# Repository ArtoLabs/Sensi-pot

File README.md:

#### Sensi-pot is open source hardware and software 
designed to help automate routine indoor garden processes such as lighting cycles, environment control, watering, and nutrient regulation. A prolific boom in the marijuana industry is taking place in Colorado, Oregon, and Washington states in the U.S. (and soon many other states) causing an increased demand for indoor gardening products. Especially in Colorado, where the winter is long and cold, most marijuana is grown indoors; necessitating equipment to help control and mimic the plant's native environment. This is especially needed for growing marijuana, which is very sensitive to heat and humidity (or lack thereof). However, most indoor gardening automation equipment is designed for big production facilities and is usually too expensive for the average grower. Sensi-pot provides electronics kits that can be easily assembled by anyone with a soldering iron, allowing the average user access to the same type of technology available to bigger growers at a fraction of the price.

# Sensi-Pot Indoor Environment Controller

This is the first Sensi-Pot open source automation device made for regulating the temperature and humidity of an enclosed space, including greenhouses. Marijuana grows best when the environment is kept at a perfect balance, and this device can maintain a perfect 55% humidity and 75 degrees fahrenheit, which is perfect for marijuana. The controller can be adjusted to regulate any temperature or level of humidity. At the heart of the device is the custom circuit board, which can be ordered using the open source Gerber files, or by [ordering through PCBway.com](https://www.pcbway.com/project/shareproject/Sensi_pot_Indoor_Environment_Controller.html) (see below for more info).

### Features

* Controls temperature to within 2 degrees.

* Controls humidity to within 5%.

* Wifi webserver shows the current temp and humidity as well as provides a manual way to active/deactivate any of the devices connected to it. You can also pause/unpause data logging from the web page as well as erase all data on the SD card.

* Data logging records the temperature and humidity with a timestamp to an SD card.

* Displays the current time, temperature and humidity on an LCD

### Hardware Specifications

* Designed using the open source PCB design and editing software, Kicad, so any changes you'd like to make to the circuit board can easily be done using the Kicad files available on Github.

* Uses the ATMEGA328P microcontroller, the same that can be found on any Arduino.

* The ATMEGA328P was programmed using the open source Arduino IDE software and uses some of the Arduino libraries in it's C++ code.

* Uses the ESP01 wifi module to serve a basic web page on the local network. To connect to a secured network the code must be modified slightly to include the SSID and the router password. The ATMEGA328P microcontroller communicates with the ESP01 using standard serial communication.

* Can technically control up to 8 devices and simply needs an 8 channel relay to do this. The pictures in this post show the controller connected to a 4 channel relay which is capable of controlling a heater, air conditioner, humidifier and dehumidifier. The other 4 devices can include lights and fans.

* Uses the DHT11 humidity and temperature sensor which can sense temperatures from 0 to 50 degrees Celsius (32 to 122 degrees Fahrenheit) +/- 2 degrees and can sense humidity from 20% to 80% +/- 5%. This can easily be replaced with no additional code with the DHT22 which has a temperature range of -40 to 125 (+/- 0.5) degrees Celsius and a humidity range of 0% to 100% (+/- 2 to 5 percent).

* Uses the MicroSD module to write logging data to any standard micro SD card. The ATMEGA328P communicates with the MicroSD module using the serial peripheral interface (SPI).

* Powered by the LM2596 adjustable buck converter which steps down any voltage between 9 and 34 volts to a regulated 5 volts used by the ATMEGA328P and it's peripheries. The voltage is further stepped down to 3.3 volts by the LM317 linear voltage regulator for use by the ESP01 wifi module. The Environment Controller consumes about 1.5 amps, with a peak current around 2 amps.

* Includes port access to programming pins via a 5 pin header that can be used to program the Environment Controller with an Arduino. Also includes access to the RX and TX pins of the ATMEGA328P so that a serial out connection can be made to a computer (mostly used for debugging).

### Software Specifications

There are actually two programs that were written to run on the Environment Controller; one for the ATMEGA328P microcontroller and one for the ESP01 wifi module which serves the webpage.

#### ATMEGA328P Software

* Programmed using the Arduino IDE and supporting libraries.

* Uses standard serial communication to transfer data between it and the ESP01 wifi module. All data is delineated by the "<" and ">" characters so that discrete amounts of data at any size can be transferred. This is very helpful as sending large amounts of data through a serial connection can be fraught with problems.

```
// Receives data from the ESP01 via serial connection
void recvESPData() {
    static boolean recvInProgress = false;
    static byte ndx = 0;
    char startMarker = '<'; // Delineate data
    char endMarker = '>';
    char rc;
    while (ESPserial.available() > 0 && newESPData == false) {
        rc = ESPserial.read();
        if (recvInProgress == true) {
            if (rc != endMarker) {
                receivedESPChars[ndx] = rc;
                ndx++;
                if (ndx >= numChars) {ndx = numChars – 1;} 
			// Step through one character at a time
            }
            else {
                receivedESPChars[ndx] = '\0'; // terminate the string
                recvInProgress = false;
                ndx = 0;
                newESPData = true;
            }
        }
        else if (rc == startMarker) {recvInProgress = true;}
    }
}
```

* Uses the Arduino `<SoftwareSerial.h>` library to communicate to the ESP01 since the RX and TX pins are still used for debugging.

* Uses the Arduino `<SD.h>` and `<SPI.h>` libraries to communicate with the MicroSD module for data logging.

```
myFile = SD.open("data.txt", FILE_WRITE); // Prepare SD card

…

    if (Tf > 74) {  //  If the temperature is greater than 74
      if (heaterActive) {
          heaterActive = false;
          logdevice =  cT + ":HE:0"; // cT is the timestamp, HE is code for heater
          lcd.setCursor(0, 1);
          lcd.print("Heat deactivated");
          if (myFile) {
            myFile.println(logdevice); // Log to SD card
          }
      }
      if ((Tf > 76) && (!acActive)){  //  If the temperature is greater than 76
          acActive = true;
          logdevice =  cT + ":AC:1";
          lcd.setCursor(0, 1);
          lcd.print("AC activated    ");
          if (myFile) {
            myFile.println(logdevice); // Log to SD card
          }
      }
    }
```
The example code block above shows how the data gets written to the SD card. Below shows how the data on the card is accessed and sent to the ESP01 to be displayed on the web page.

```
void getSDdata () { // Fetches the logging data from the SD card and prints it
                    // to the ESP01 via serial
    myFile = SD.open("/data.txt", FILE_READ);
    if(myFile) {
        ESPserial.print("<");
        while (myFile.available()) {
          ESPserial.write(myFile.read());
        }
        ESPserial.println(">");
        myFile.close();
    }
    else {
      lcd.setCursor(0, 1);
      lcd.print("Error reading SD"); 
    }
}
```
* Uses the `<LiquidCrystal.h>` library to display data on the LCD.

* Uses the `<SimpleDHT.h>` library to fetch temperature and humidity data from the sensor.

* A binary system was created to utilize the shift register. Since there are eight possible devices that can be controlled, all 8 outputs of the shift register are used. A binary number contains 8 digits, where a 1 indicates that a device is on, and a 0 indicates a devices is off. Binary math (xor) is used to add all the binary states of each device together to create one binary number that represents the state of all devices.

```
const byte relay1 = 0x80; //0b10000000    HUMIDIFIER      green
const byte relay2 = 0x40; //0b01000000    DE-HUMIDIFIER   red
const byte relay3 = 0x20; //0b00100000    HEATER          yellow
const byte relay4 = 0x10; //0b00010000    AC              green
const byte relay5 = 0x08; //0b00001000    FAN 1
const byte relay6 = 0x04; //0b00000100    FAN 2
const byte relay7 = 0x02; //0b00000010    FAN 3
const byte relay8 = 0x01; //0b00000001    FAN 4
void activateDevice () {
  state = allOff; 
  if (humidifierActive) { state = relay1; }
  if (dehumidifierActive) { state = state xor relay2; }
  if (heaterActive) { state = state xor relay3; }
  if (acActive) { state = state xor relay4; }
  state = allOn - state; // The shift register needs the opposite: On = 0, Off = 1
  writeReg(state);
}
```

#### ESP01 Software

* Programmed using the Arduino IDE and supporting libraries.

* Contains a small amount of CSS and HTML stored in `rawliteral` memory used to display the web page.

```
const char* FORM_HEADER = R"rawliteral(
<div id="side"><form id='theform' action='http://)rawliteral";

const char* FORM_MIDDLE = R"rawliteral(' method='POST'>
<a href='#' onClick="document.getElementById('ARG').value='2'; document.getElementById('theform').submit();">
<div class="btn">Get SD Data</div></a>
<a href='#' onClick="document.getElementById('ARG').value='1'; document.getElementById('theform').submit();">
<div class="btn">Delete SD Data</div></a>
)rawliteral";

const char* UNPAUSED = R"rawliteral(
<a href='#' onClick="document.getElementById('ARG').value='3'; document.getElementById('theform').submit();">
<div class="btn">Pause Logging</div></a>
)rawliteral";

const char* PAUSED = R"rawliteral(
<a href='#' onClick="document.getElementById('ARG').value='3'; document.getElementById('theform').submit();">
<div class="btn">Resume Logging</div></a>
)rawliteral";

const char* FORM_FOOTER = R"rawliteral(
<input type='hidden' name='ARG' id='ARG'>
<input type='hidden' name='ARG2' id='ARG2'>
</form></div>
)rawliteral";
```
* Uses the `<time.h>` and `<TimeLib.h>` libraries to fetch the current time from the Internet (time.nist.gov) and sets it local time by this. This is used to create the Unix timestamps for logging, and to convert Unix timestamps to human readable days, minutes, hours and the date. 

* The ESP01 libraries handle form submission on the web page, but a custom function was created to parse the data and commence the action.

```
void handleSubmit() {
  String Davalue;
  String dev;
  Davalue = server.arg("ARG");
  dev = server.arg("ARG2");
  if (Davalue == "1") {       // Delete all data on the SD card
    Serial.println("<2>");    // Returns a success code to the ATMEGA328P (only indicates code was received)
    time_t timer = time(nullptr);
    while (!Serial.available()) { 
      time_t now = time(nullptr);  // Every action has a 10 second timeout period
      if (now > timer + 10) {
        startPage();
        makeSideBar();
        makePageTop();
        server.sendContent("<div id='content'><h3>Could not delete data</h3></div>");
        makePageBottom();
        dataErr = true;
        break; 
      }
    }
    if (!dataErr) {
      startPage();
      makeSideBar();
      makePageTop();
      server.sendContent("<div id='content'><h3>SD card has been deleted</h3></div>");
      makePageBottom();
      dataErr = false;
    }
  }
  else if (Davalue == "2") {  // Retieves the logging data from the SD card and display it on the webpage
    Serial.print("<1>");      // Send the success code to the ATMEGA328P (only indicates code was received)
    waitForData = true;
    time_t timer = time(nullptr);  // 10 second timeout period
    while (!Serial.available()) { 
      time_t now = time(nullptr);
      if (now > timer + 10) {
        startPage();
        makeSideBar();
        makePageTop();
        server.sendContent("<div id='content'><h3>Could not get data</h3></div>");
        makePageBottom();
        waitForData == false;
        break; 
      }
    }
  }
  else if (Davalue == "3") {  // Pauses logging
    Serial.print("<5>");
    time_t timer = time(nullptr);   // 10 second timeout period
    while (!Serial.available()) {
      time_t now = time(nullptr);
      if (now > timer + 10) {
        startPage();
        makeSideBar();
        makePageTop();
        server.sendContent("<div id='content'><h3>Logging could not be paused</h3></div>");
        makePageBottom();
        break; 
      }
    }
  }
  else if (Davalue == "4") {  // Changes the on/off state of a device when the user clicks a button
    Serial.print("<D");
    Serial.print(dev);
    Serial.print(">");
    time_t timer = time(nullptr);
    while (!Serial.available()) {
      time_t now = time(nullptr);
      if (now > timer + 10) {
        startPage();
        makeSideBar();
        makePageTop();
        server.sendContent("<div id='content'><h3>Device could not be reached</h3></div>");
        makePageBottom();
        break; 
      }
    }
  }
  else {returnFail("Bad value");}
}
```

* The ESP01 is used by the ATMEGA328P to request the current timestamp each time data is logged.

```
      if (receivedChars[0] == '1') {  // The single digit code 1 requests the current time
                                      // This request is used for data logging
          time_t t = time(nullptr);
          int seconds = (int) t;
          char ds[10];
          itoa(seconds,ds,10);      // the time is sent as a UNIX timestamp
          Serial.print ("<");
          for(int i=0;i<10;i++) {
            Serial.print(ds[i]);    // Send the data back to ATMEGA328P
          }
          Serial.print (">");
      }
      else if (receivedChars[0] == '2') { // Code 2 requests the ESP01 sets it's own time to the current time
                                          // This request is used for displaying the time and date
          time_t t = time(nullptr);
          setTime(t);
          char buf[20];
          sprintf(buf,"%d-%02d-%02d %02d:%02d:%02d", year(), month(),
          day(), hour(), minute(), second());
          Serial.print ("<");
          for(int i=0;i<20;i++) {
            Serial.print(buf[i]);
          }
          Serial.print (">");
      }
```

### Assembling The Sensi-Pot Indoor Environment Controller

The circuit board has on it a lable for every part, so assembling and soldering should be very simple. A complete BOM (Bill of Materials) is included in the Github repository so ordering all the parts should also be relatively easy. A complete set of assembly instructions along with a "how-to" video will be created in the near future. 

#### [Order this circuit board from PCBway.com](https://www.pcbway.com/project/shareproject/Sensi_pot_Indoor_Environment_Controller.html)
Since Artolabs uses PCBway.com for it's circuit board production you can take advantage of PCBway's share program and simply order this circuit board without the need to submit the Gerber files! You [get 5 circuit boards for $5](https://www.pcbway.com/project/shareproject/Sensi_pot_Indoor_Environment_Controller.html) (plus about $8 shipping), and Artolabs gets a small commission too. 

ArtoLabs uses PCBway.com exclusively for small run production and prototyping. They provide outstanding customer service, and carefully review each order. It was surprising and comforting when they found some very small details I had overlooked and gave me a chance to correct my boards before manufacturing them.

#### Technology Stack

Sensi-Pot uses the Arduino open source library, Kicad open source PCB design software, and is written in C++.

#### Roadmap

This is obviously a working prototype. There are actually an incredible number of improvements planned for the Sensi-Pot Environment Controller, including an alarm circuit (for notifying when the temperature or humidity has gone out of control, perhaps due to a malfunctioning device), an LDR (Light Detecting Resistor) to enable the LCD and LEDs to power off when the grow area is in the "lights out" phase of the day, a soft power up circuit to prevent the shift register from activating when the Environment Controller is switched on, and too many more to mention. Sensi-Pot also has in the works a Soil Sensor Array to monitor the soil conditions of up to 10 plants per array, as well as many more automation devices.

#### Contact

Please contact Mike (Mike-A) on Discord
https://discord.gg/97GKVFC

#### Additional Resources
https://github.com/arduino/Arduino
https://github.com/KiCad

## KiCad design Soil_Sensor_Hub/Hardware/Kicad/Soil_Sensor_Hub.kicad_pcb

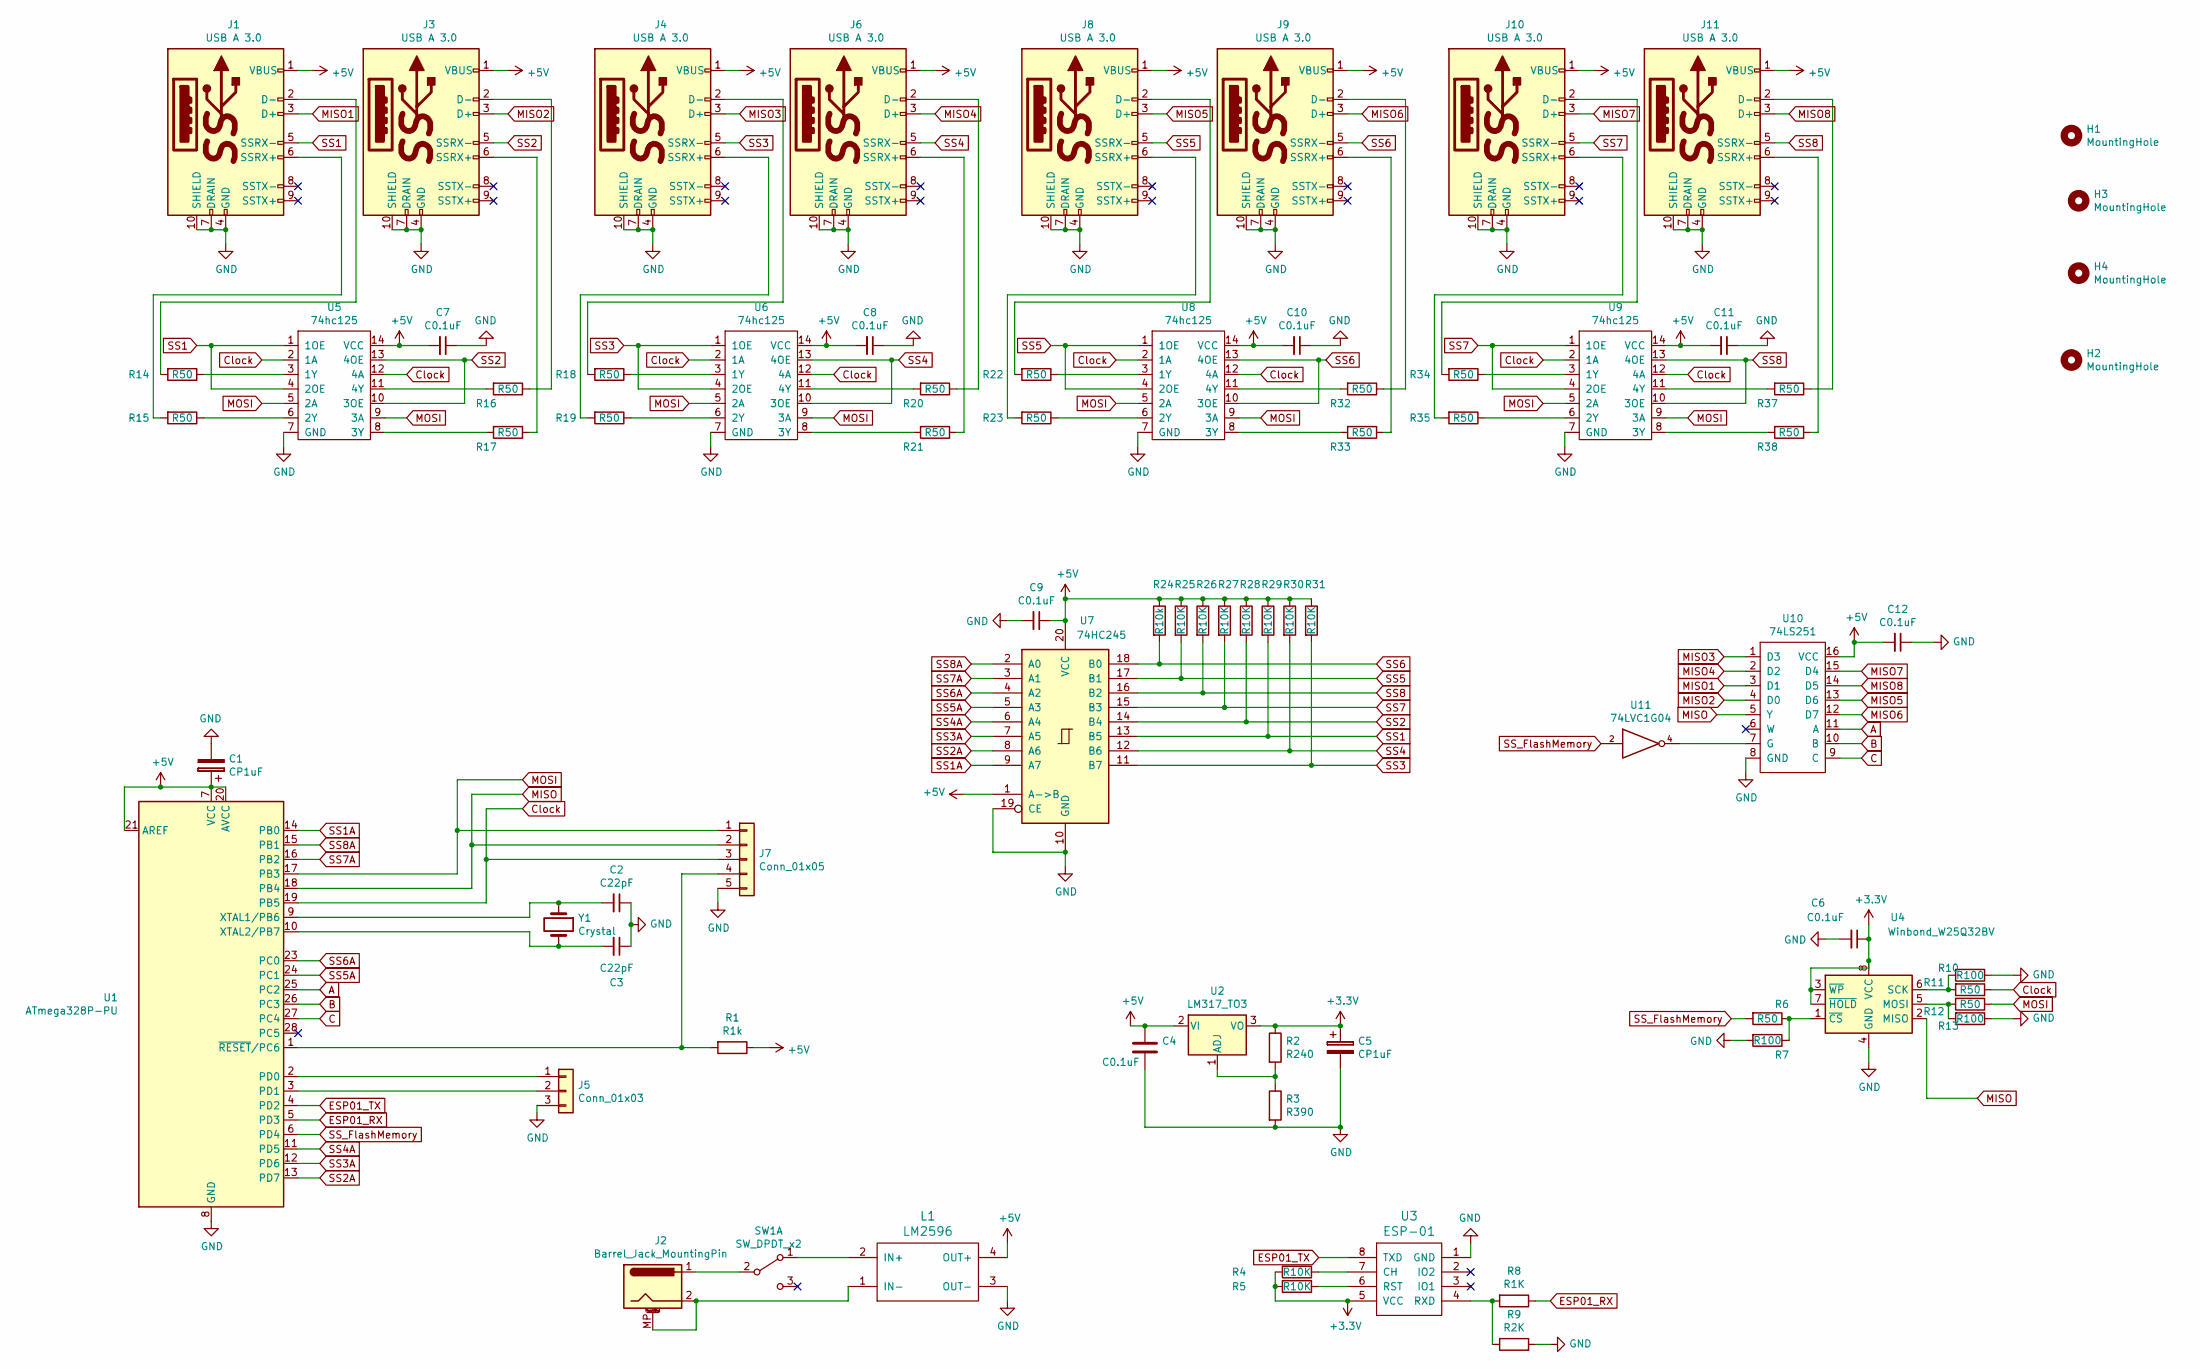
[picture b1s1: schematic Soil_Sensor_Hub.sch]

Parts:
C1, C5: CP1uF; CP_Radial_D4.0mm_P1.50mm_bigger_pads
C2, C3: C22pF; C_Disc_D3.0mm_W1.6mm_P2.50mm
C4, C6, C7, C8, C9, C10, C11, C12: C0.1uF; C_Disc_D3.0mm_W1.6mm_P2.50mm
H1, H2, H3, H4: MountingHole; MountingHole_3.2mm_M3
J1, J3, J4, J6, J8, J9, J10, J11: USB A 3.0; USB3_A_Molex_Edited
J2: Barrel_Jack_MountingPin; BarrelJack_Horizontal
J5: Conn_01x03; PinHeader_1x03_P2.54mm_Vertical
J7: Conn_01x05; PinHeader_1x05_P2.54mm_Vertical
L1: LM2596; LM2596_Module
R1: R1k; R_Axial_DIN0204_L3.6mm_D1.6mm_P7.62mm_Horizontal_bigger_pads
R2: R240; R_Axial_DIN0204_L3.6mm_D1.6mm_P7.62mm_Horizontal_bigger_pads
R3: R390; R_Axial_DIN0204_L3.6mm_D1.6mm_P7.62mm_Horizontal_bigger_pads
R4, R5, R25, R26, R27, R28, R29, R30, R31: R10K; R_Axial_DIN0204_L3.6mm_D1.6mm_P7.62mm_Horizontal_bigger_pads
R6, R11, R12, R14, R15, R16, R17, R18, R19, R20, R21, R22, R23, R32, R33, R34, R35, R37, R38: R50; R_Axial_DIN0204_L3.6mm_D1.6mm_P7.62mm_Horizontal_bigger_pads
R7, R10, R13: R100; R_Axial_DIN0204_L3.6mm_D1.6mm_P7.62mm_Horizontal_bigger_pads
R8: R1K; R_Axial_DIN0204_L3.6mm_D1.6mm_P7.62mm_Horizontal_bigger_pads
R9: R2K; R_Axial_DIN0204_L3.6mm_D1.6mm_P7.62mm_Horizontal_bigger_pads
R24: R10k; R_Axial_DIN0204_L3.6mm_D1.6mm_P7.62mm_Horizontal_bigger_pads
SW1: SW_DPDT_x2; PinHeader_1x03_P2.54mm_Vertical
U1: ATmega328P-PU; DIP-28_W7.62mm
U2: LM317_TO3; TO-220-3_Vertical
U3: ESP-01
U4: Winbond_W25Q32BV; SOIC-8_3.9x4.9mm_P1.27mm
U5, U6, U8, U9: 74hc125; DIP-14_W7.62mm
U7: 74HC245; DIP-20_W7.62mm
U10: 74LS251; DIP-16_W7.62mm
U11: 74LVC1G04; SOT-23-5_HandSoldering
Y1: Crystal; Crystal_HC18-U_Vertical

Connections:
+3V3: C5.1, C6.1, R2.1, R4.2, R5.2, U2.3 (VO), U3.5 (VCC), U4.3 (~WP), U4.7 (~HOLD), U4.8 (VCC)
+5V: C1.1, C4.1, C7.2, C8.2, C9.1, C10.2, C11.2, C12.2, J1.1 (VBUS), J3.1 (VBUS), J4.1 (VBUS), J6.1 (VBUS), J8.1 (VBUS), J9.1 (VBUS), J10.1 (VBUS), J11.1 (VBUS), L1.4 (OUT+), R1.1, R24.1, R25.1, R26.1, R27.1, R28.1, R29.1, R30.1, R31.1, U1.7 (VCC), U1.20 (AVCC), U1.21 (AREF), U2.2 (VI), U5.14 (VCC), U6.14 (VCC), U7.1 (A->B), U7.20 (VCC), U8.14 (VCC), U9.14 (VCC), U10.16 (VCC)
A: U1.25 (PC2), U10.11 (A)
B: U1.26 (PC3), U10.10 (B)
C: U1.27 (PC4), U10.9 (C)
Clock: J7.3, R11.1, U1.19 (PB5), U5.2 (1A), U5.12 (4A), U6.2 (1A), U6.12 (4A), U8.2 (1A), U8.12 (4A), U9.2 (1A), U9.12 (4A)
ESP01_RX: R8.1, U1.5 (PD3)
ESP01_TX: U1.4 (PD2), U3.8 (TXD)
GND: C1.2, C2.1, C3.1, C4.2, C5.2, C6.2, C7.1, C8.1, C9.2, C10.1, C11.1, C12.1, J1.4 (GND), J1.7 (DRAIN), J1.10 (SHIELD), J3.4 (GND), J3.7 (DRAIN), J3.10 (SHIELD), J4.4 (GND), J4.7 (DRAIN), J4.10 (SHIELD), J5.3, J6.4 (GND), J6.7 (DRAIN), J6.10 (SHIELD), J7.5, J8.4 (GND), J8.7 (DRAIN), J8.10 (SHIELD), J9.4 (GND), J9.7 (DRAIN), J9.10 (SHIELD), J10.4 (GND), J10.7 (DRAIN), J10.10 (SHIELD), J11.4 (GND), J11.7 (DRAIN), J11.10 (SHIELD), L1.3 (OUT-), R3.2, R7.2, R9.2, R10.1, R13.1, U1.8 (GND), U1.22 (GND), U3.1 (GND), U4.4 (GND), U5.7 (GND), U6.7 (GND), U7.10 (GND), U7.19 (CE), U8.7 (GND), U9.7 (GND), U10.8 (GND), U11.3 (GND)
MISO: J7.2, U1.18 (PB4), U4.2 (MISO), U10.5 (Y)
MISO1: J1.3 (D+), U10.3 (D1)
MISO2: J3.3 (D+), U10.4 (D0)
MISO3: J4.3 (D+), U10.1 (D3)
MISO4: J6.3 (D+), U10.2 (D2)
MISO5: J8.3 (D+), U10.13 (D6)
MISO6: J9.3 (D+), U10.12 (D7)
MISO7: J10.3 (D+), U10.15 (D4)
MISO8: J11.3 (D+), U10.14 (D5)
MOSI: J7.1, R12.1, U1.17 (PB3), U5.5 (2A), U5.9 (3A), U6.5 (2A), U6.9 (3A), U8.5 (2A), U8.9 (3A), U9.5 (2A), U9.9 (3A)
unnamed: C2.2, U1.9 (XTAL1/PB6), Y1.1
unnamed: C3.2, U1.10 (XTAL2/PB7), Y1.2
unnamed: J1.2 (D-), R14.2
unnamed: J1.6 (SSRX+), R15.2
unnamed: J2.1, SW1.2 (B)
unnamed: J2.2, J2.MP (MountPin), L1.1 (IN-)
unnamed: J3.2 (D-), R16.1
unnamed: J3.6 (SSRX+), R17.1
unnamed: J4.2 (D-), R18.2
unnamed: J4.6 (SSRX+), R19.2
unnamed: J5.1, U1.2 (PD0)
unnamed: J5.2, U1.3 (PD1)
unnamed: J6.2 (D-), R20.1
unnamed: J6.6 (SSRX+), R21.1
unnamed: J7.4, R1.2, U1.1 (~RESET~/PC6)
unnamed: J8.2 (D-), R22.2
unnamed: J8.6 (SSRX+), R23.2
unnamed: J9.2 (D-), R32.1
unnamed: J9.6 (SSRX+), R33.1
unnamed: J10.2 (D-), R34.2
unnamed: J10.6 (SSRX+), R35.2
unnamed: J11.2 (D-), R37.1
unnamed: J11.6 (SSRX+), R38.1
unnamed: L1.2 (IN+), SW1.1 (A)
unnamed: R2.2, R3.1, U2.1 (ADJ)
unnamed: R4.1, U3.7 (CH)
unnamed: R5.1, U3.6 (RST)
unnamed: R6.1, R7.1, U4.1 (~CS)
unnamed: R8.2, R9.1, U3.4 (RXD)
unnamed: R10.2, R11.2, U4.6 (SCK)
unnamed: R12.2, R13.2, U4.5 (MOSI)
unnamed: R14.1, U5.3 (1Y)
unnamed: R15.1, U5.6 (2Y)
unnamed: R16.2, U5.11 (4Y)
unnamed: R17.2, U5.8 (3Y)
unnamed: R18.1, U6.3 (1Y)
unnamed: R19.1, U6.6 (2Y)
unnamed: R20.2, U6.11 (4Y)
unnamed: R21.2, U6.8 (3Y)
unnamed: R22.1, U8.3 (1Y)
unnamed: R23.1, U8.6 (2Y)
unnamed: R32.2, U8.11 (4Y)
unnamed: R33.2, U8.8 (3Y)
unnamed: R34.1, U9.3 (1Y)
unnamed: R35.1, U9.6 (2Y)
unnamed: R37.2, U9.11 (4Y)
unnamed: R38.2, U9.8 (3Y)
unnamed: U10.7 (G), U11.4
SS1: J1.5 (SSRX-), R29.2, U5.1 (1OE), U5.4 (2OE), U7.13 (B5)
SS1A: U1.14 (PB0), U7.9 (A7)
SS2: J3.5 (SSRX-), R28.2, U5.10 (3OE), U5.13 (4OE), U7.14 (B4)
SS2A: U1.13 (PD7), U7.8 (A6)
SS3: J4.5 (SSRX-), R31.2, U6.1 (1OE), U6.4 (2OE), U7.11 (B7)
SS3A: U1.12 (PD6), U7.7 (A5)
SS4: J6.5 (SSRX-), R30.2, U6.10 (3OE), U6.13 (4OE), U7.12 (B6)
SS4A: U1.11 (PD5), U7.6 (A4)
SS5: J8.5 (SSRX-), R25.2, U7.17 (B1), U8.1 (1OE), U8.4 (2OE)
SS5A: U1.24 (PC1), U7.5 (A3)
SS6: J9.5 (SSRX-), R24.2, U7.18 (B0), U8.10 (3OE), U8.13 (4OE)
SS6A: U1.23 (PC0), U7.4 (A2)
SS7: J10.5 (SSRX-), R27.2, U7.15 (B3), U9.1 (1OE), U9.4 (2OE)
SS7A: U1.16 (PB2), U7.3 (A1)
SS8: J11.5 (SSRX-), R26.2, U7.16 (B2), U9.10 (3OE), U9.13 (4OE)
SS8A: U1.15 (PB1), U7.2 (A0)
SS_FlashMemory: R6.2, U1.6 (PD4), U11.2
VCC: U11.5 (VCC)

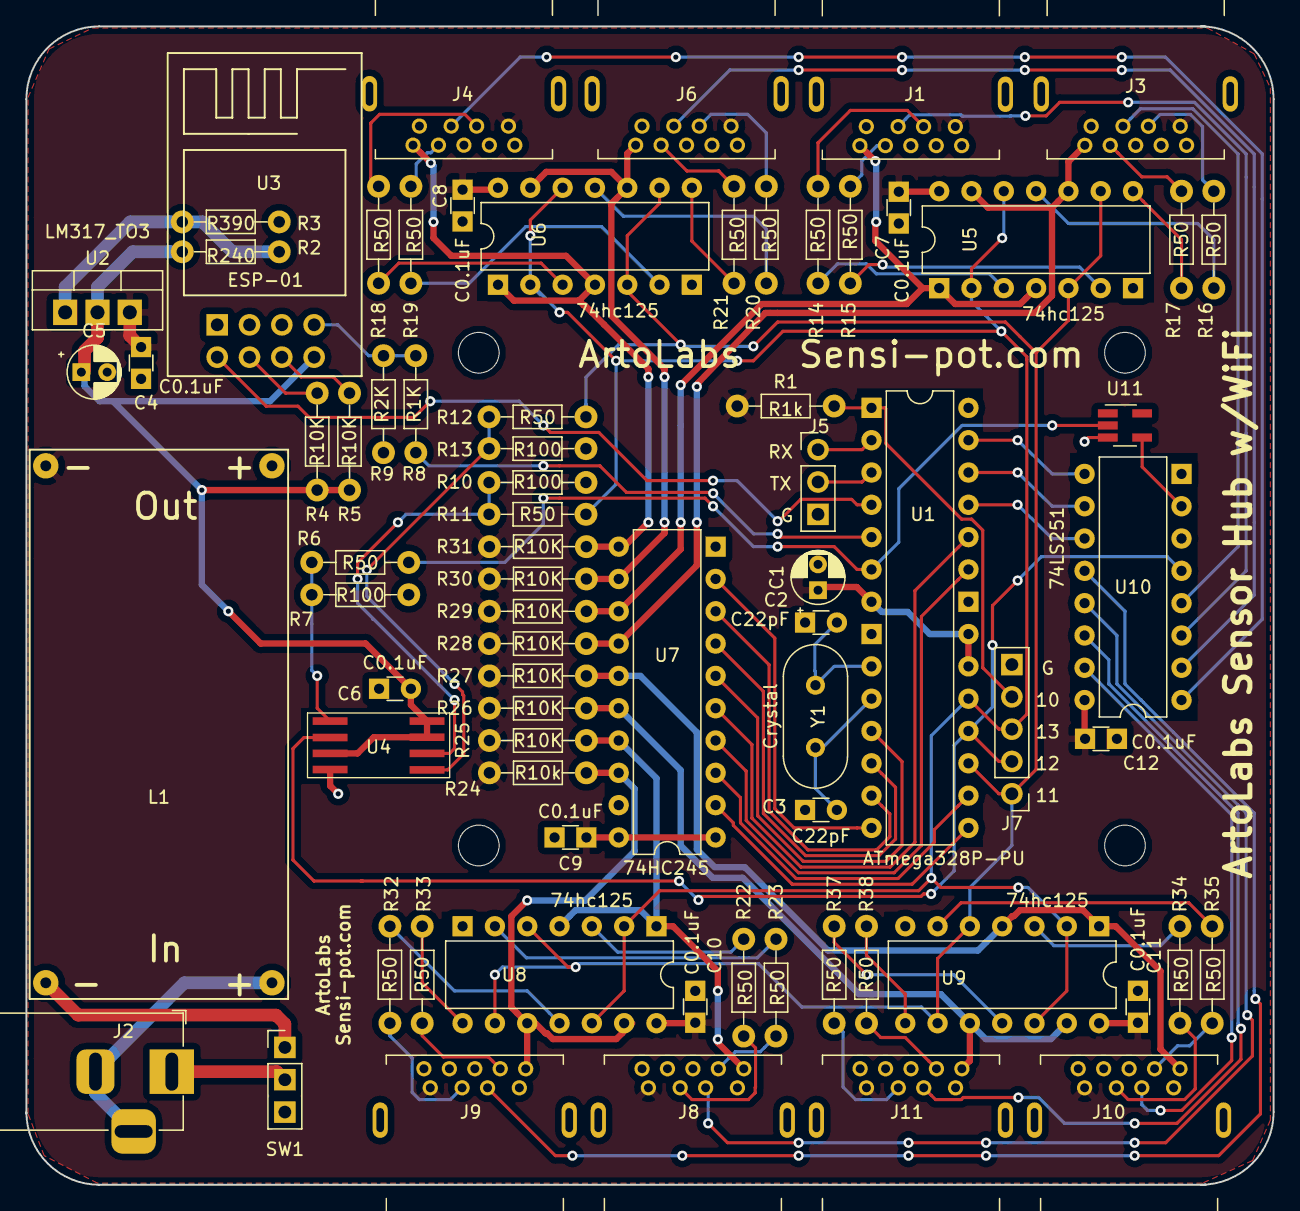
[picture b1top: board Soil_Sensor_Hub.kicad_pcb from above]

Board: 2 copper layers, 98.0 x 91.1 mm, 78 parts (0 on the bottom side), 84 nets.

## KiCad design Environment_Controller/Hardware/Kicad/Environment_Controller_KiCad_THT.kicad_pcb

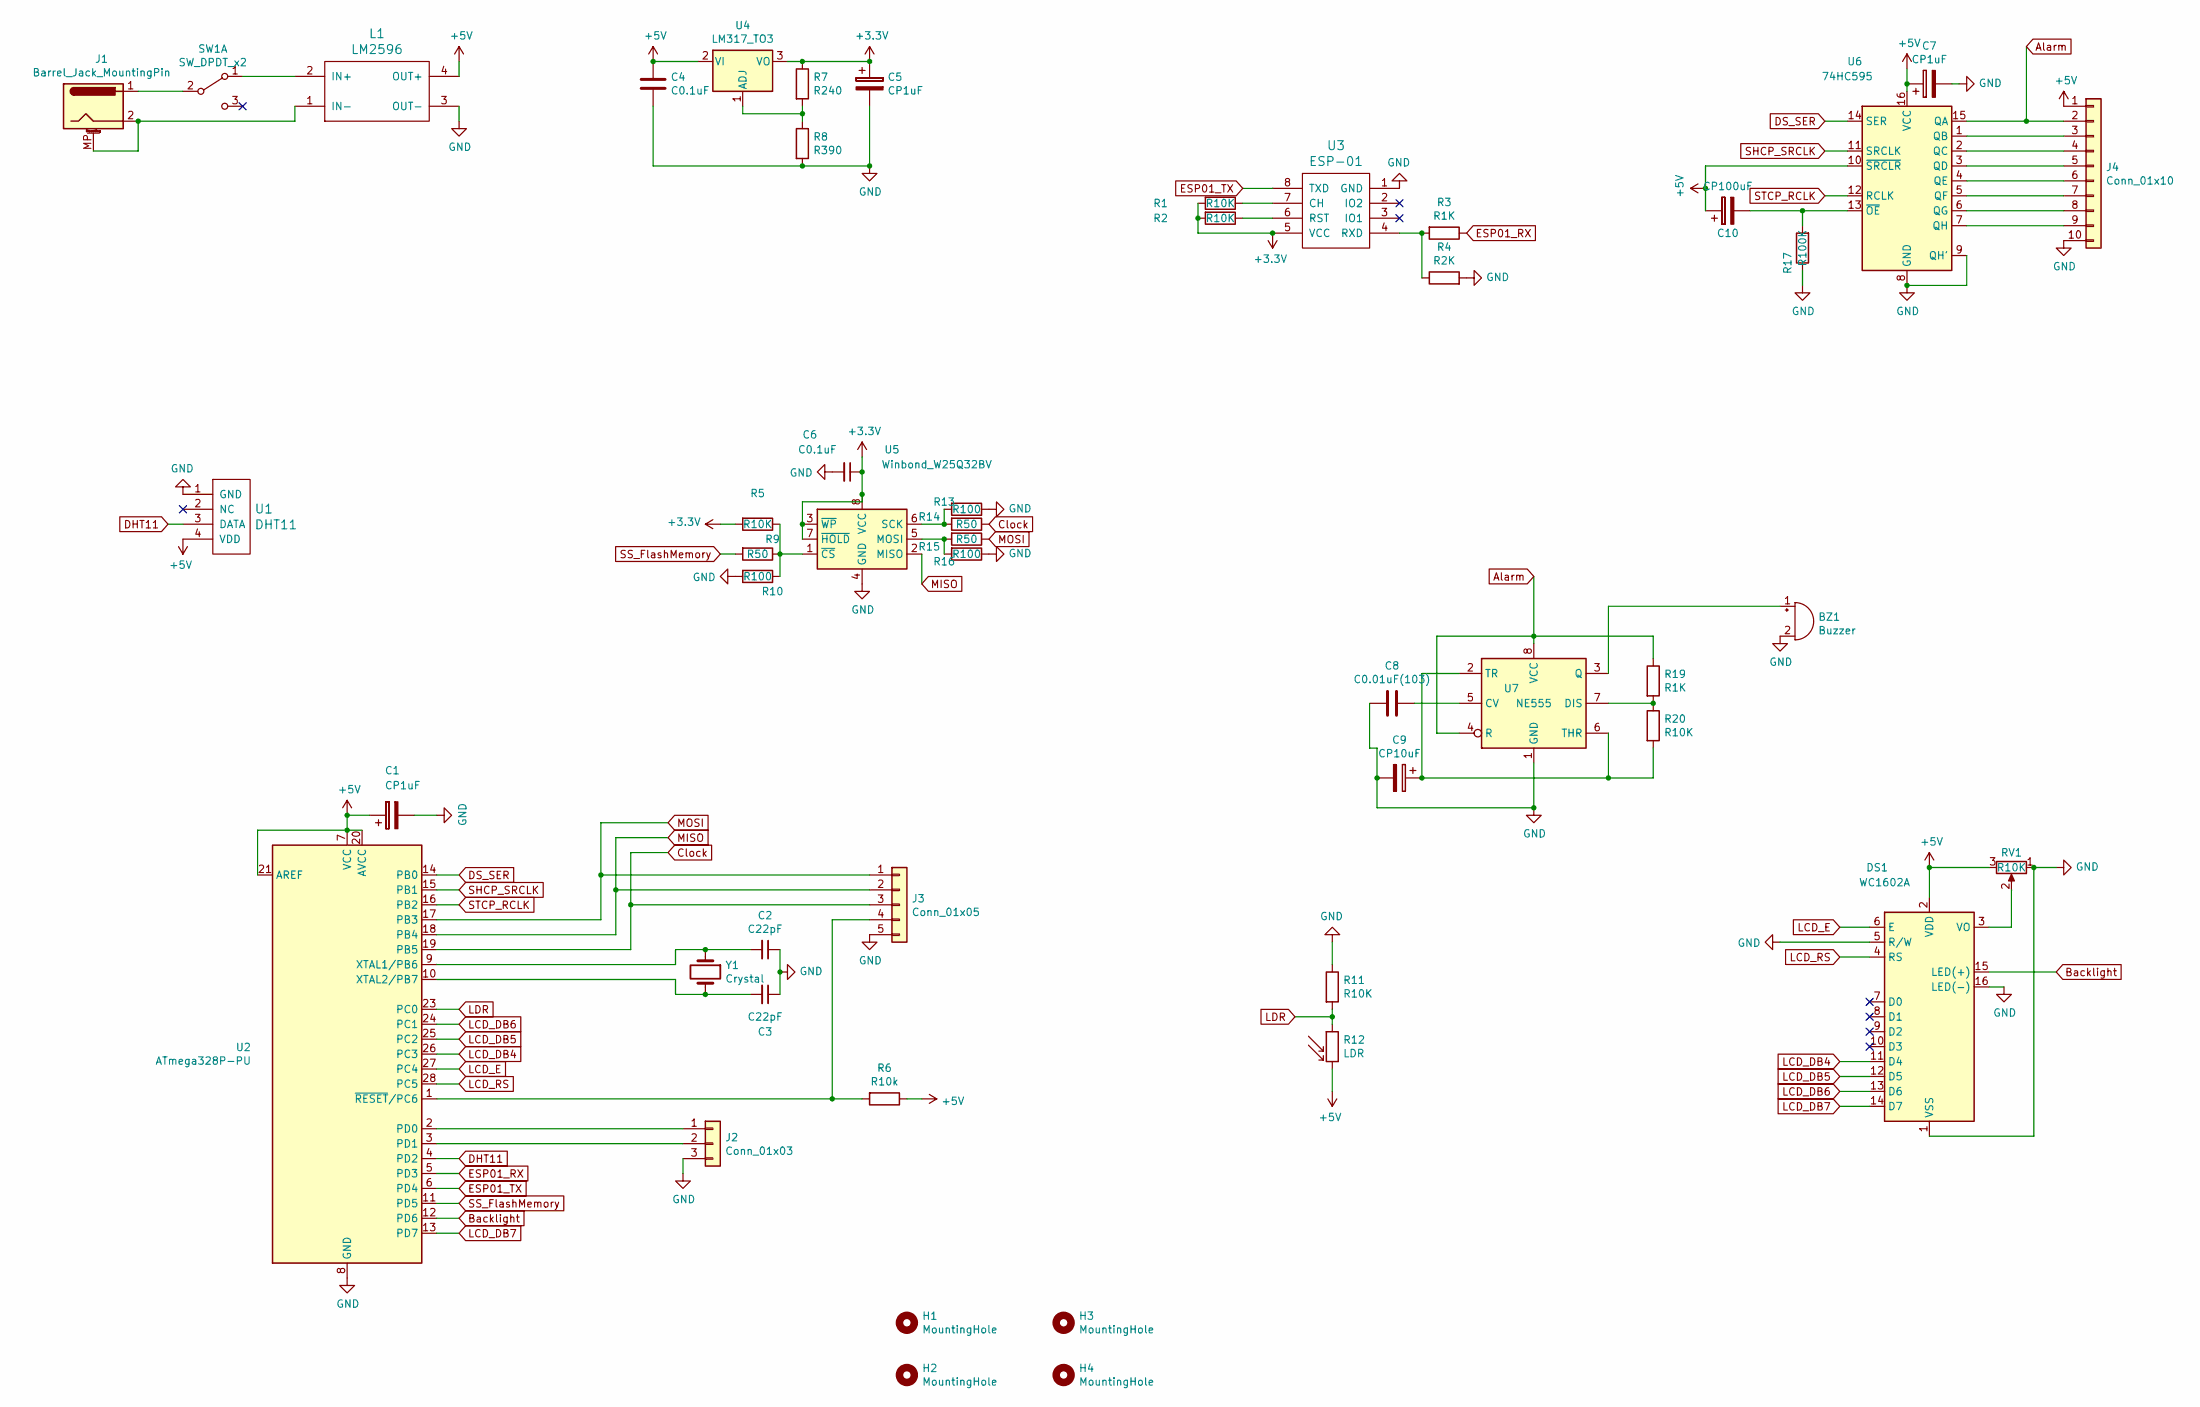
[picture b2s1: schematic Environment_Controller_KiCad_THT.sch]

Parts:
BZ1: Buzzer; Buzzer_12x9.5RM7.6
C1, C5, C7: CP1uF; CP_Radial_D4.0mm_P1.50mm_bigger_pads
C2, C3: C22pF; C_Disc_D3.0mm_W1.6mm_P2.50mm
C4, C6: C0.1uF; C_Disc_D3.0mm_W1.6mm_P2.50mm
C8: C0.01uF(103); C_Disc_D3.0mm_W1.6mm_P2.50mm
C9: CP10uF; CP_Radial_D4.0mm_P1.50mm_bigger_pads
C10: CP100uF; CP_Radial_D5.0mm_P2.50mm
DS1: WC1602A
H1, H2, H3, H4: MountingHole; MountingHole_3.2mm_M3
J1: Barrel_Jack_MountingPin; BarrelJack_Horizontal
J2: Conn_01x03; PinHeader_1x03_P2.54mm_Vertical
J3: Conn_01x05; PinHeader_1x05_P2.54mm_Vertical
J4: Conn_01x10; PinHeader_1x10_P2.54mm_Vertical
L1: LM2596; LM2596_Module
R1, R2, R5, R11, R20: R10K; R_Axial_DIN0204_L3.6mm_D1.6mm_P7.62mm_Horizontal_bigger_pads
R3, R19: R1K; R_Axial_DIN0204_L3.6mm_D1.6mm_P7.62mm_Horizontal_bigger_pads
R4: R2K; R_Axial_DIN0204_L3.6mm_D1.6mm_P7.62mm_Horizontal_bigger_pads
R6: R10k; R_Axial_DIN0204_L3.6mm_D1.6mm_P7.62mm_Horizontal_bigger_pads
R7: R240; R_Axial_DIN0204_L3.6mm_D1.6mm_P7.62mm_Horizontal_bigger_pads
R8: R390; R_Axial_DIN0204_L3.6mm_D1.6mm_P7.62mm_Horizontal_bigger_pads
R9, R14, R15: R50; R_Axial_DIN0204_L3.6mm_D1.6mm_P7.62mm_Horizontal_bigger_pads
R10, R13, R16: R100; R_Axial_DIN0204_L3.6mm_D1.6mm_P7.62mm_Horizontal_bigger_pads
R12: LDR; R_Axial_DIN0204_L3.6mm_D1.6mm_P1.90mm_Vertical
R17: R100K; R_Axial_DIN0204_L3.6mm_D1.6mm_P7.62mm_Horizontal_bigger_pads
RV1: R10K; Potentiometer_Bourns_3296W_Vertical
SW1: SW_DPDT_x2; PinHeader_1x03_P2.54mm_Vertical
U1: DHT11; PinHeader_1x04_P2.54mm_Vertical
U2: ATmega328P-PU; DIP-28_W7.62mm
U3: ESP-01
U4: LM317_TO3; TO-220-3_Vertical
U5: Winbond_W25Q32BV; SOIC-8_3.9x4.9mm_P1.27mm
U6: 74HC595; DIP-16_W7.62mm
U7: NE555; DIP-8_W7.62mm
Y1: Crystal; Crystal_HC18-U_Vertical

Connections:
+3V3: C5.1, C6.1, R1.2, R2.2, R5.2, R7.1, U3.5 (VCC), U4.3 (VO), U5.3 (~WP), U5.7 (~HOLD), U5.8 (VCC)
+5V: C1.1, C4.1, C7.1, C10.1, DS1.2 (VDD), J4.1, L1.4 (OUT+), R6.1, R12.2, RV1.3, U1.4 (VDD), U2.7 (VCC), U2.20 (AVCC), U2.21 (AREF), U4.2 (VI), U6.10 (~SRCLR), U6.16 (VCC)
Alarm: J4.2, R19.1, U6.15 (QA), U7.4 (R), U7.8 (VCC)
Backlight: DS1.15 (LED(+)), U2.12 (PD6)
Clock: J3.3, R14.1, U2.19 (PB5)
DHT11: U1.3 (DATA), U2.4 (PD2)
DS_SER: U2.14 (PB0), U6.14 (SER)
ESP01_RX: R3.1, U2.5 (PD3)
ESP01_TX: U2.6 (PD4), U3.8 (TXD)
GND: BZ1.2 (+), C1.2, C2.1, C3.1, C4.2, C5.2, C6.2, C7.2, C8.2, C9.2, DS1.1 (VSS), DS1.5 (R/W), DS1.16 (LED(-)), J2.3, J3.5, J4.10, L1.3 (OUT-), R4.2, R8.2, R10.2, R11.1, R13.1, R16.1, R17.1, RV1.1, U1.1 (GND), U2.8 (GND), U2.22 (GND), U3.1 (GND), U5.4 (GND), U6.8 (GND), U6.9 (QH'), U7.1 (GND)
LCD_DB4: DS1.11 (D4), U2.26 (PC3)
LCD_DB5: DS1.12 (D5), U2.25 (PC2)
LCD_DB6: DS1.13 (D6), U2.24 (PC1)
LCD_DB7: DS1.14 (D7), U2.13 (PD7)
LCD_E: DS1.6 (E), U2.27 (PC4)
LCD_RS: DS1.4 (RS), U2.28 (PC5)
LDR: R11.2, R12.1, U2.23 (PC0)
MISO: J3.2, U2.18 (PB4), U5.2 (MISO)
MOSI: J3.1, R15.1, U2.17 (PB3)
unnamed: BZ1.1 (-), U7.3 (Q)
unnamed: C2.2, U2.9 (XTAL1/PB6), Y1.1
unnamed: C3.2, U2.10 (XTAL2/PB7), Y1.2
unnamed: C8.1, U7.5 (CV)
unnamed: C9.1, R20.2, U7.2 (TR), U7.6 (THR)
unnamed: C10.2, R17.2, U6.13 (~OE)
unnamed: DS1.3 (VO), RV1.2
unnamed: J1.1, SW1.2 (B)
unnamed: J1.2, J1.MP (MountPin), L1.1 (IN-)
unnamed: J2.1, U2.2 (PD0)
unnamed: J2.2, U2.3 (PD1)
unnamed: J3.4, R6.2, U2.1 (~RESET~/PC6)
unnamed: J4.3, U6.1 (QB)
unnamed: J4.4, U6.2 (QC)
unnamed: J4.5, U6.3 (QD)
unnamed: J4.6, U6.4 (QE)
unnamed: J4.7, U6.5 (QF)
unnamed: J4.8, U6.6 (QG)
unnamed: J4.9, U6.7 (QH)
unnamed: L1.2 (IN+), SW1.1 (A)
unnamed: R1.1, U3.7 (CH)
unnamed: R2.1, U3.6 (RST)
unnamed: R3.2, R4.1, U3.4 (RXD)
unnamed: R7.2, R8.1, U4.1 (ADJ)
unnamed: R5.1, R9.1, R10.1, U5.1 (~CS)
unnamed: R13.2, R14.2, U5.6 (SCK)
unnamed: R15.2, R16.2, U5.5 (MOSI)
unnamed: R19.2, R20.1, U7.7 (DIS)
SHCP_SRCLK: U2.15 (PB1), U6.11 (SRCLK)
SS_FlashMemory: R9.2, U2.11 (PD5)
STCP_RCLK: U2.16 (PB2), U6.12 (RCLK)

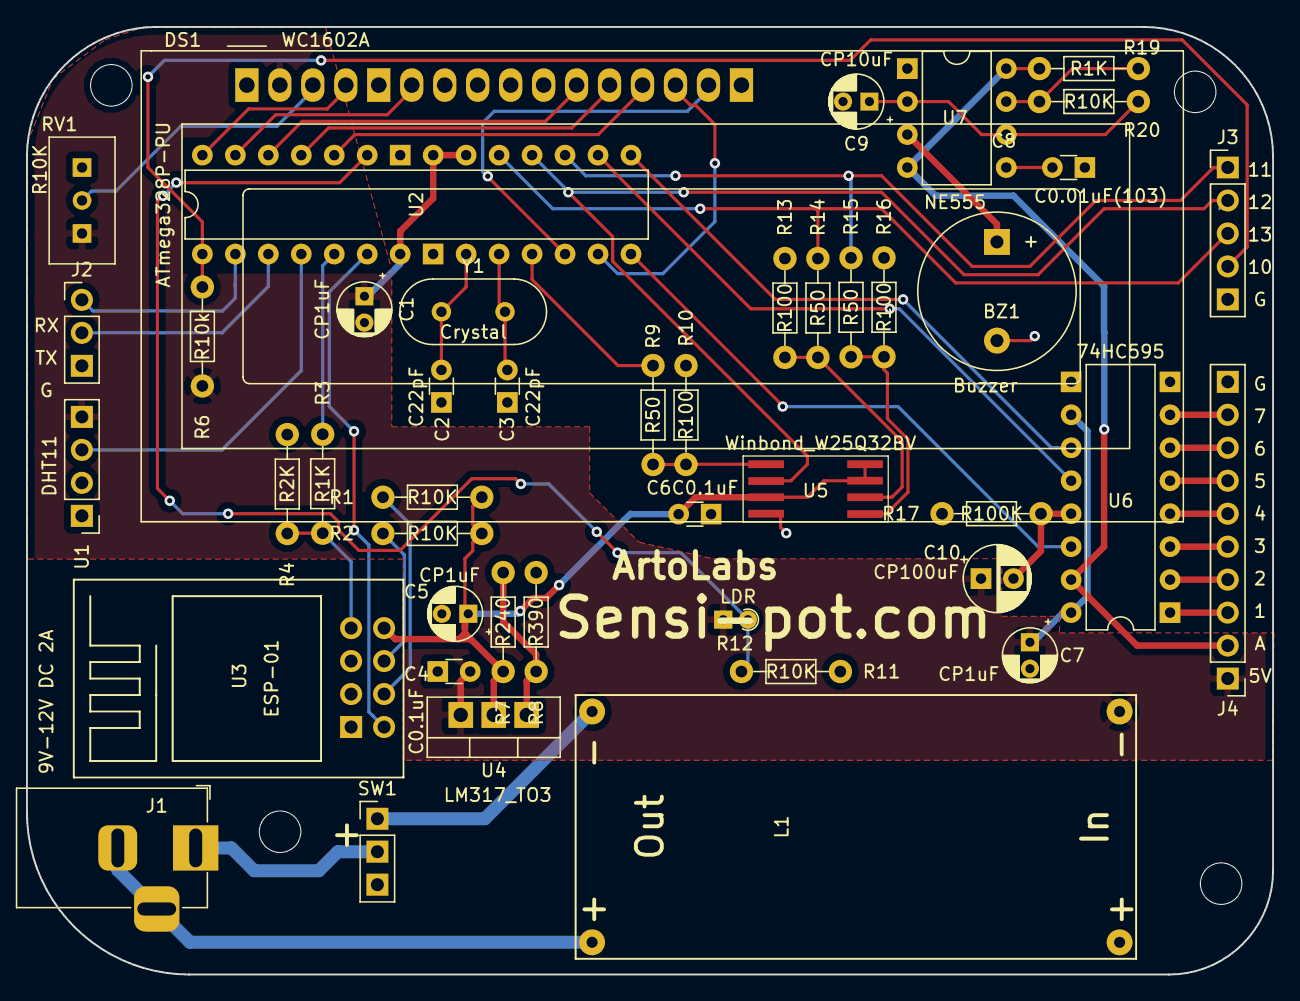
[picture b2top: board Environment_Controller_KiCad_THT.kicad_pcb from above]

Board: 2 copper layers, 96.0 x 73.0 mm, 49 parts (0 on the bottom side), 50 nets.
